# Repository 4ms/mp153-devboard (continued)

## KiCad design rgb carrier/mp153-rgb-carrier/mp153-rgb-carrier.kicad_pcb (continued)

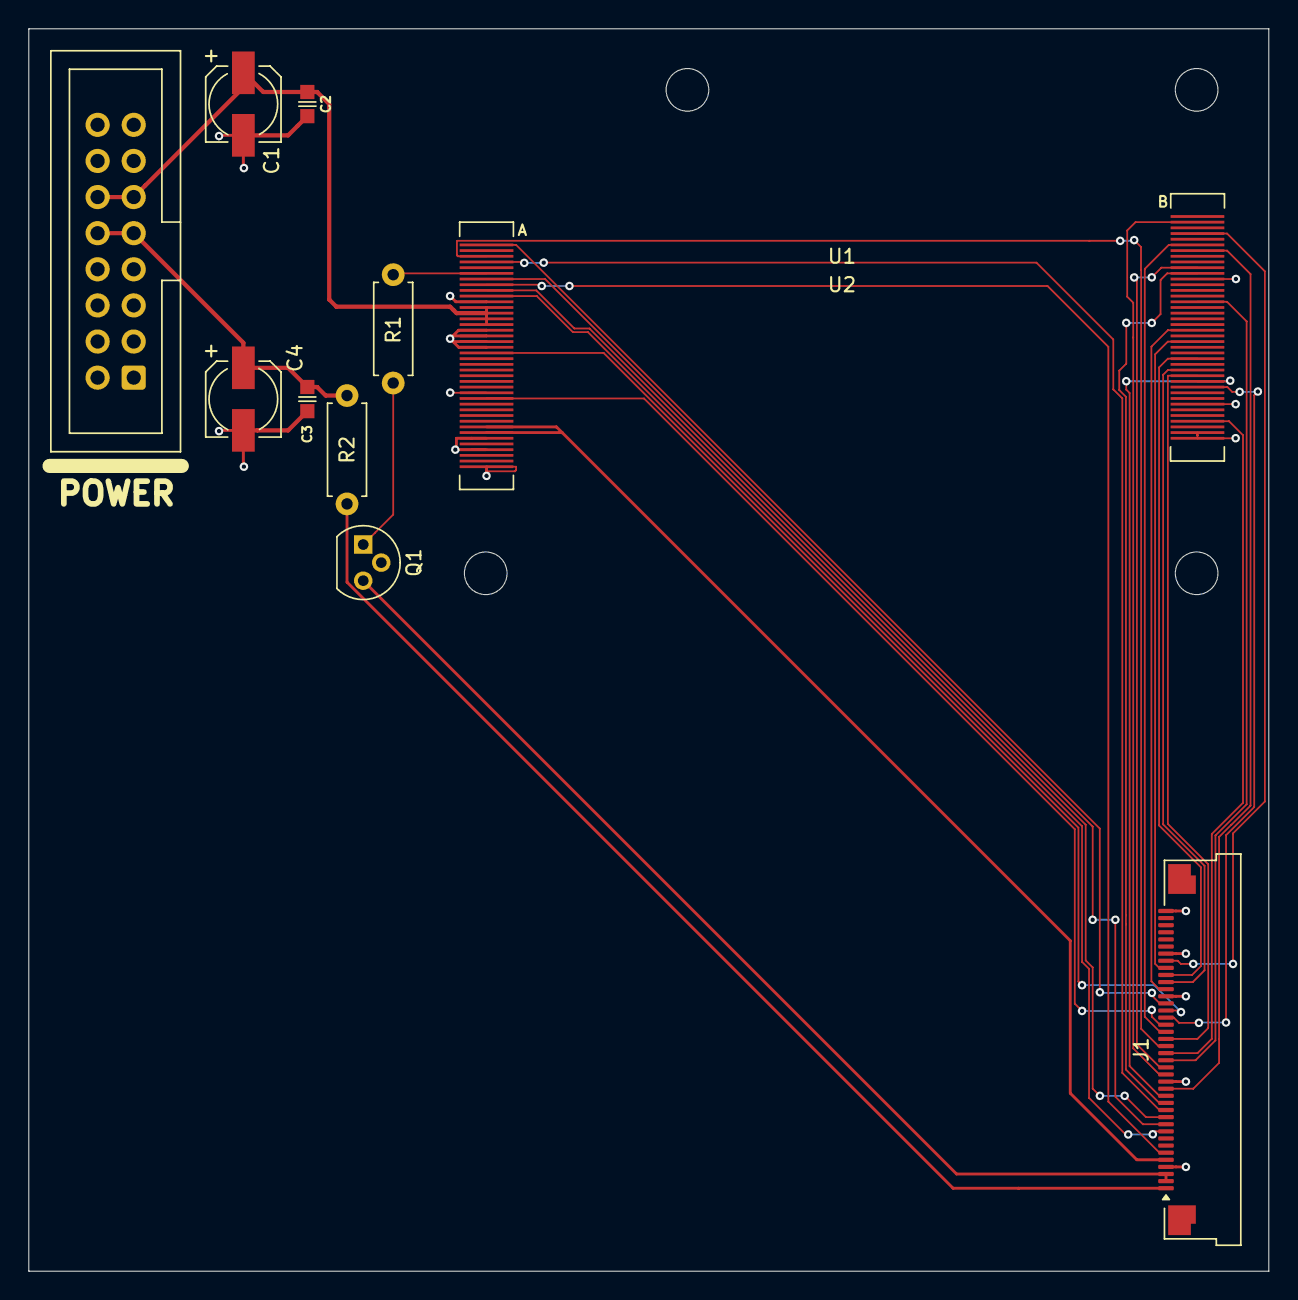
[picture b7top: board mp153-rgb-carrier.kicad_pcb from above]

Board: 2 copper layers, 87.2 x 87.4 mm, 11 parts (0 on the bottom side), 32 nets.

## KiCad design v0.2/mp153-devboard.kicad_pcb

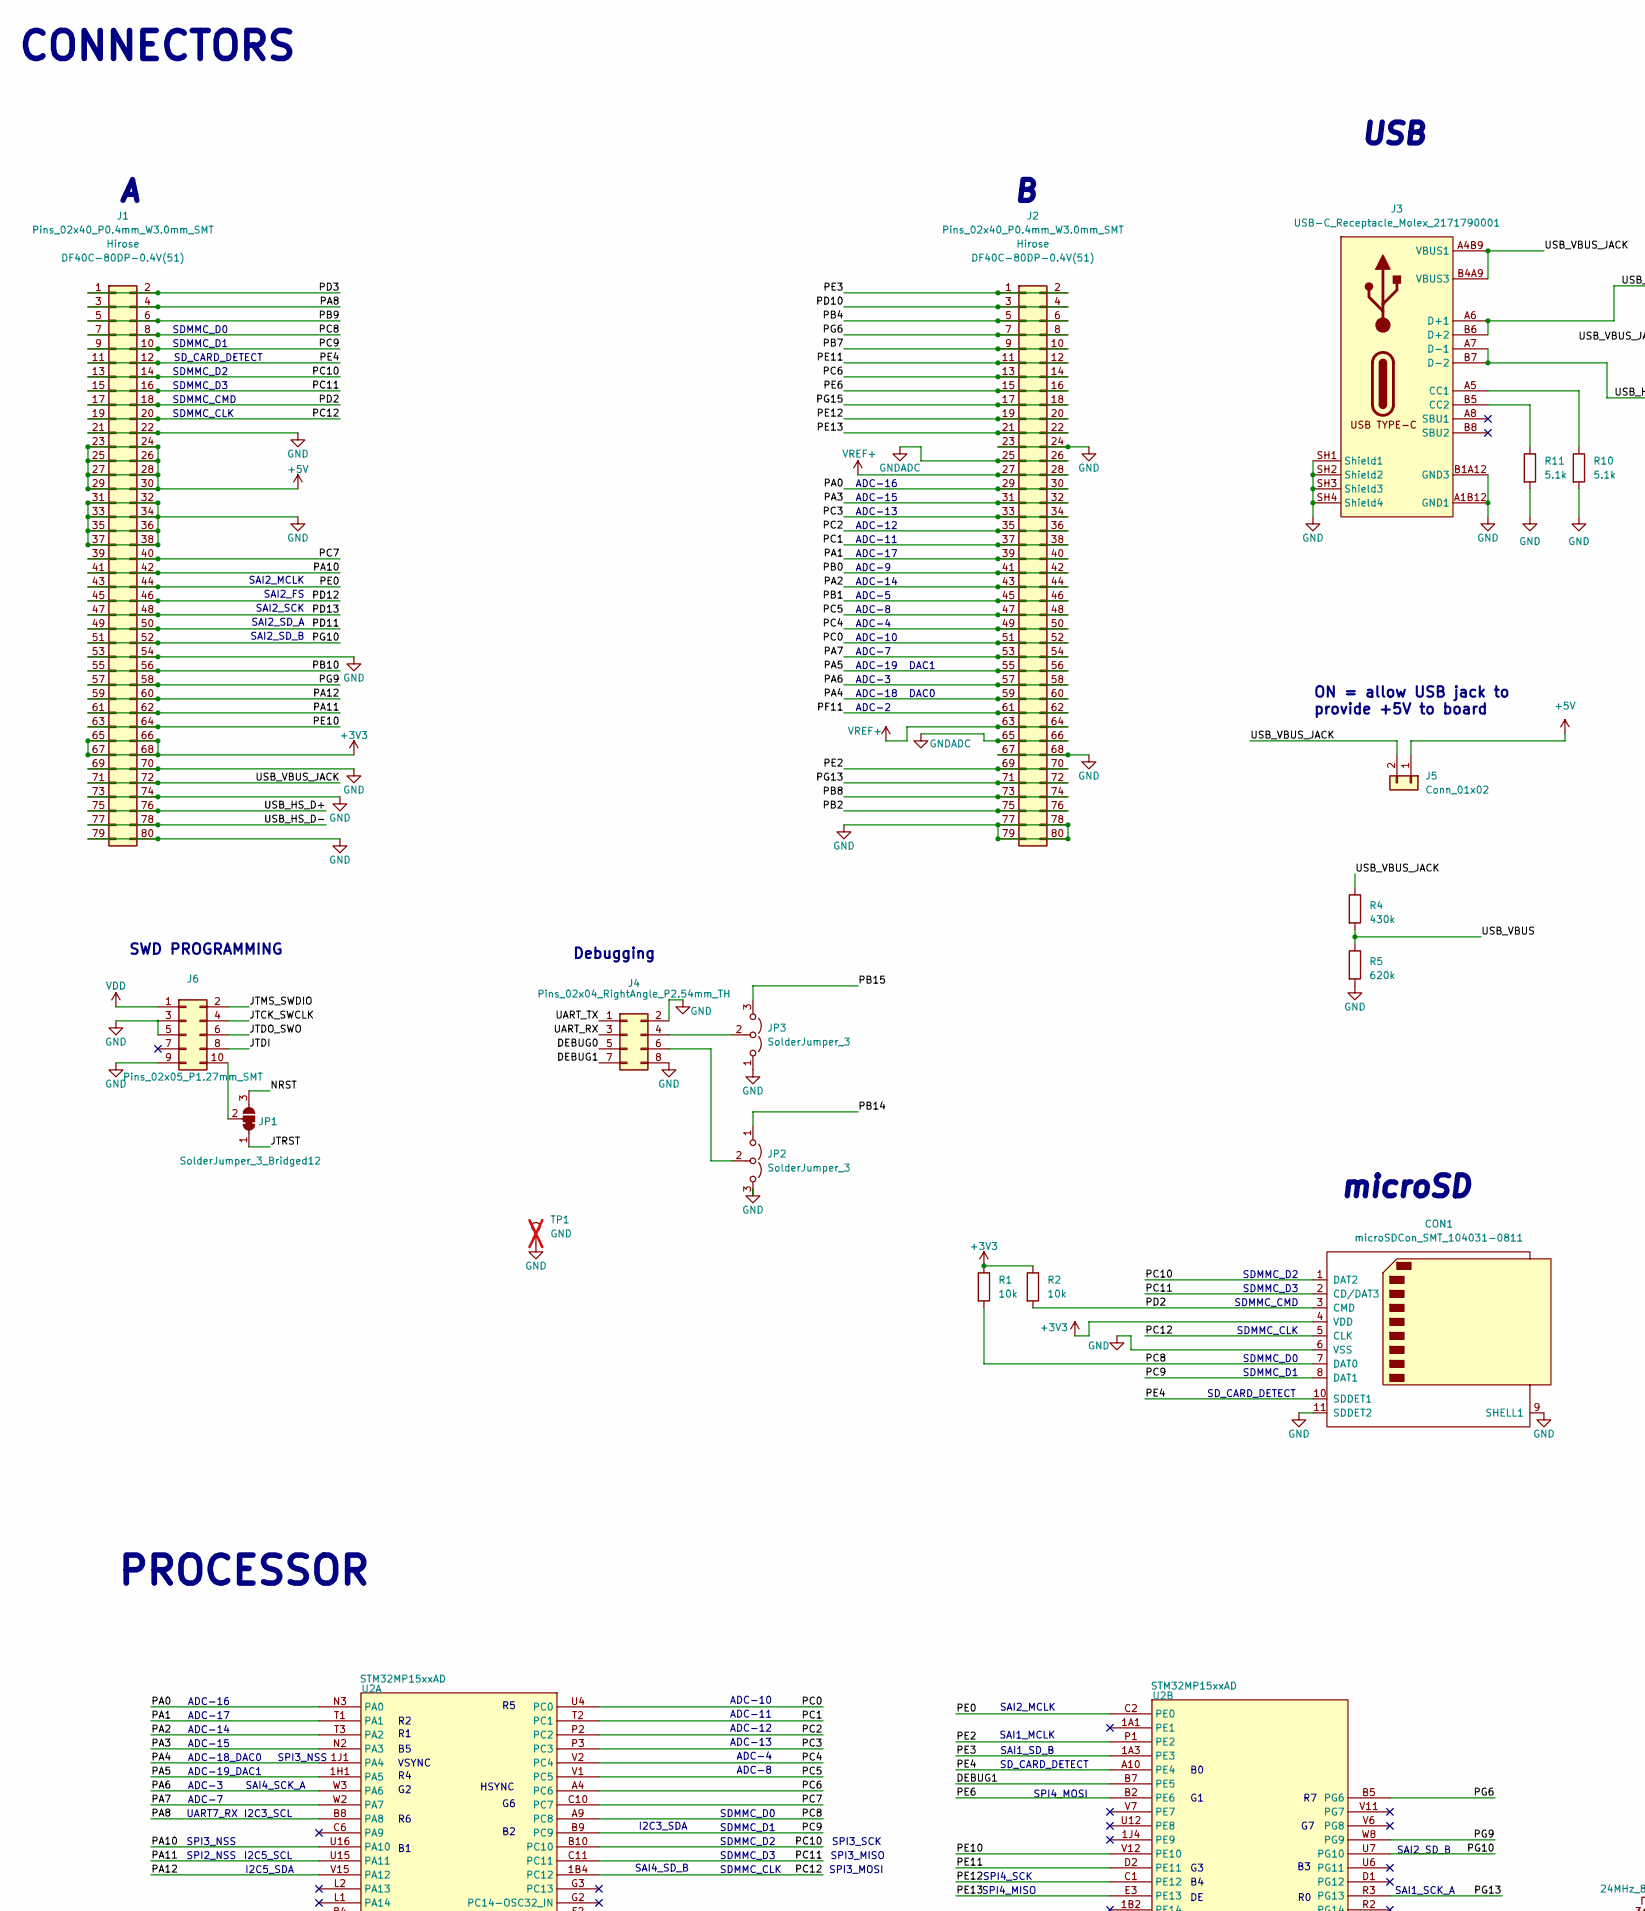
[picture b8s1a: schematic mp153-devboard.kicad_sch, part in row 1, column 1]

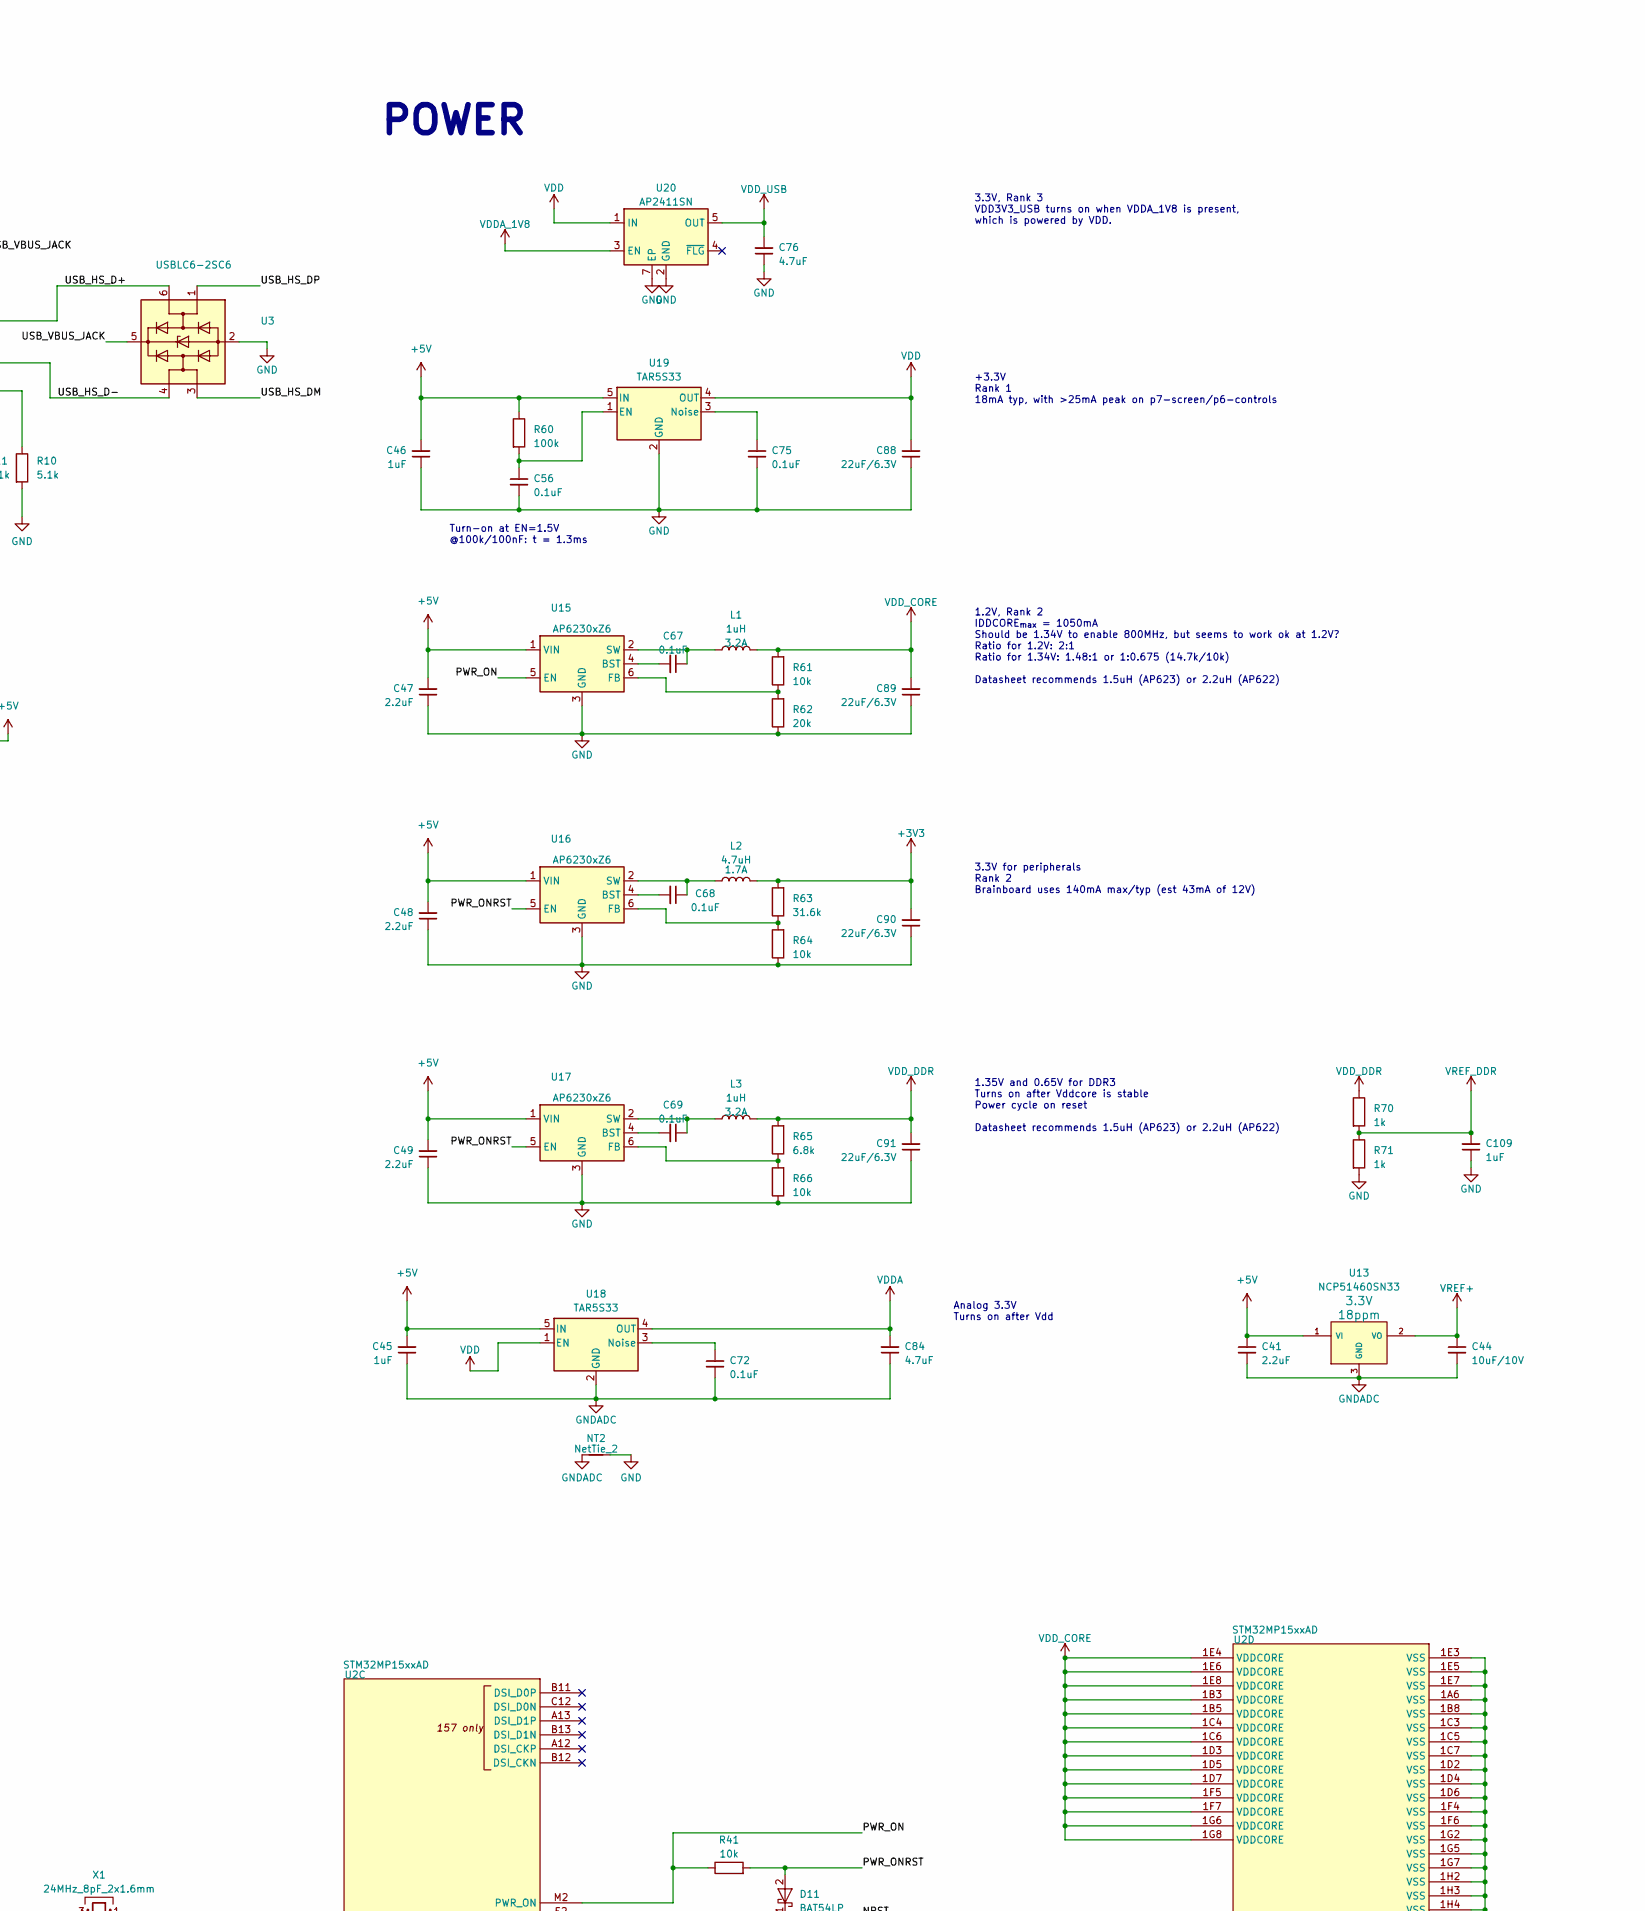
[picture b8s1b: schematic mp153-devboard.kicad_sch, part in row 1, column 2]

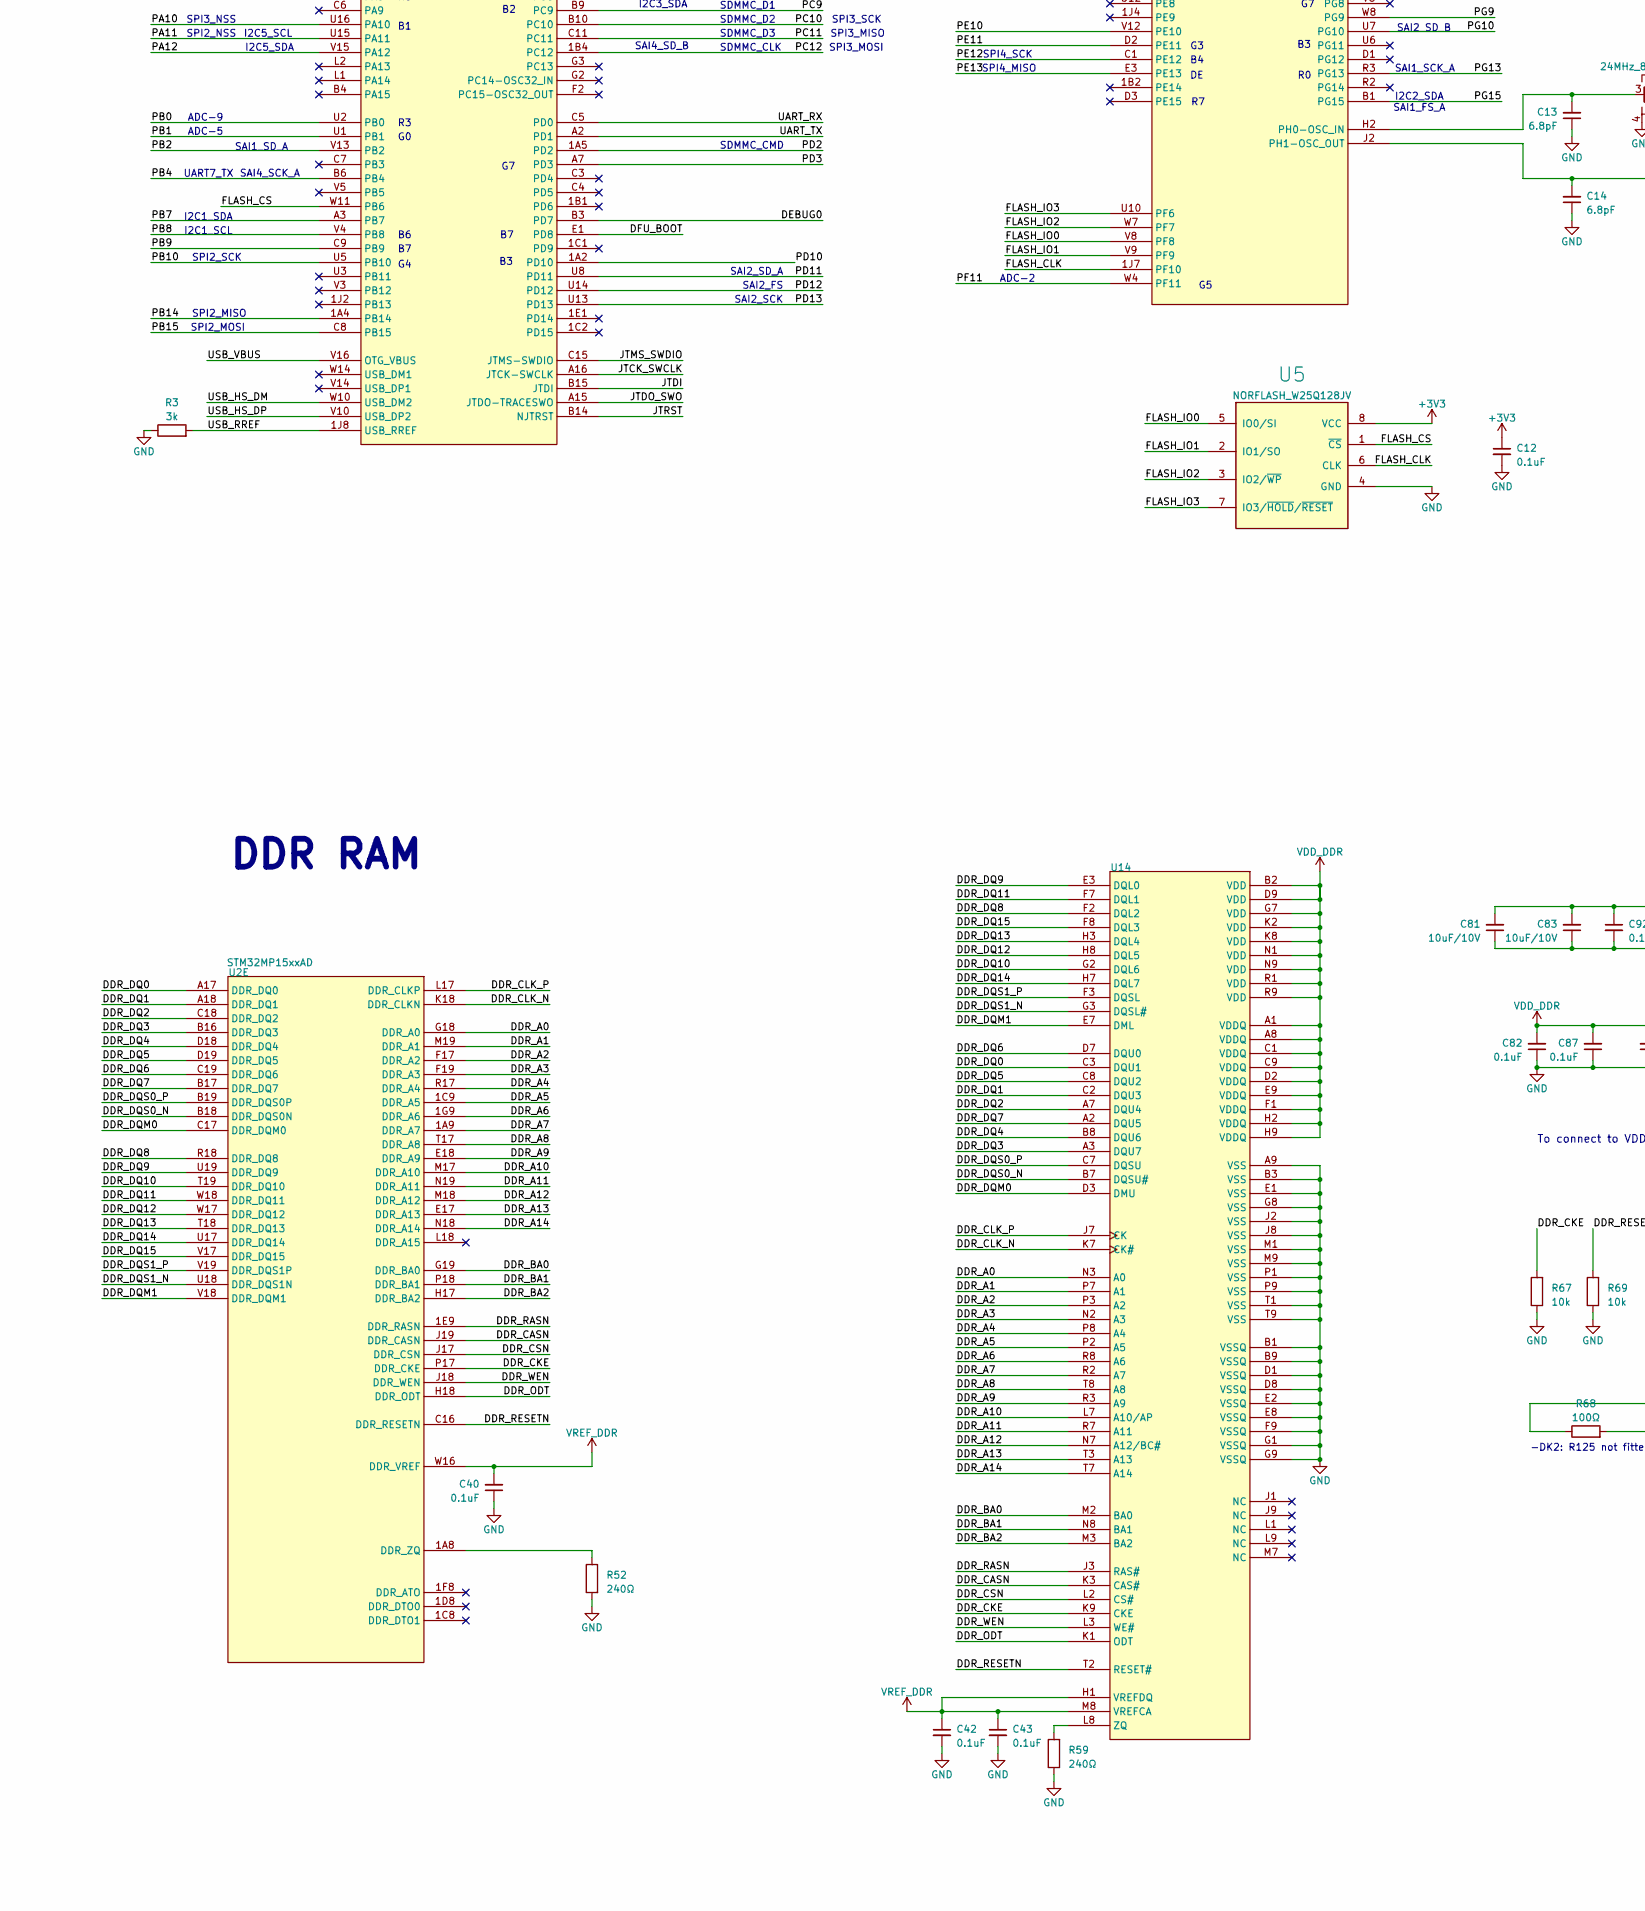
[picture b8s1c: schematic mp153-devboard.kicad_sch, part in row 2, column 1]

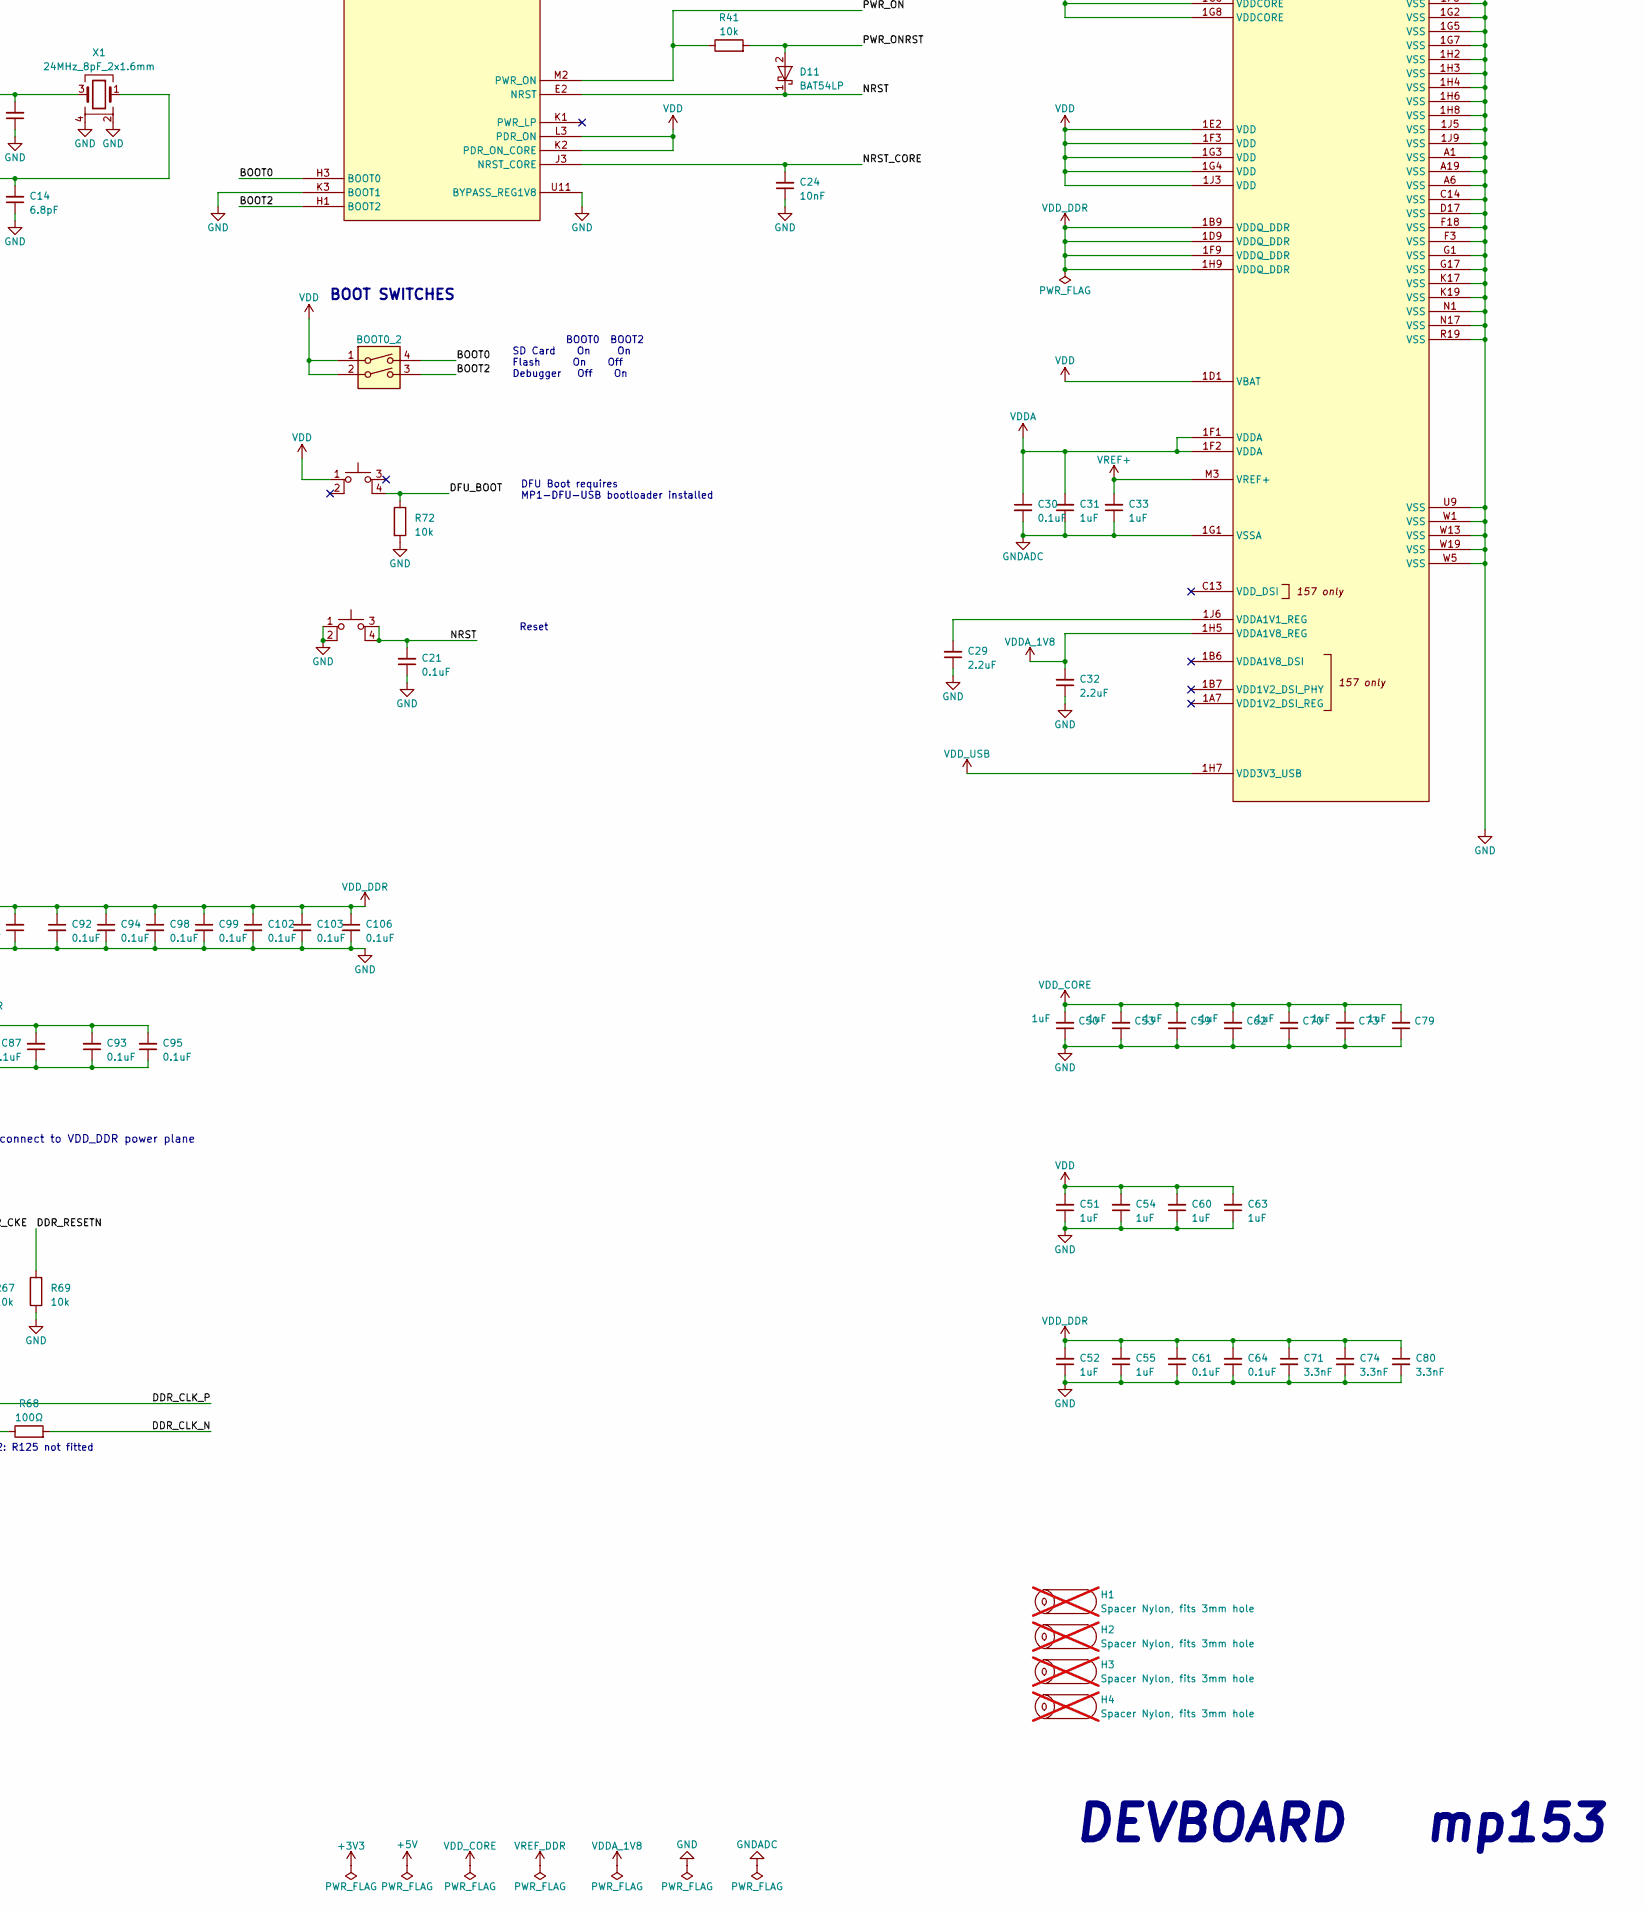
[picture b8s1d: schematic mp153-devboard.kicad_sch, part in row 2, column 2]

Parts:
BOOT0_2: SW_DIP_x02_CTS_219-2MST; SW_DIP_SPSTx02_CTS_219-2MSTR; Part Number 219-2MST; JLCPCB ID C2961978
C12, C21, C30, C40, C42, C43, C61, C64, C67, C68, C69, C82, C87, C92, C93, C94, C95, C98, C99, C102, C103, C106: 100nF_0402_16V; C_0402; Part Number GCM155R71C104KA55D; JLCPCB ID C1525
C13, C14: 6.8pF_0402_25V; C_0402; Part Number CC0402CRNPO9BN6R8; JLCPCB ID C1576
C24: 10nF_0402_16V; C_0402; Part Number CC0402KRX7R7BB103; JLCPCB ID C15195
C29, C32: 2.2uF_0402_6.3V; C_0402; Part Number GRM155R60J225KE95D; JLCPCB ID C12530
C31, C33, C45, C46, C50, C51, C52, C53, C54, C55, C59, C60, C62, C63, C70, C73, C79, C109: 1uF_0402_25V; C_0402; Part Number GMK105CC6105KV-F; JLCPCB ID C52923
C41, C47, C48, C49: 2.2uF_0603_25V; C_0603; Part Number GRM188R6YA225KA12D; JLCPCB ID C57895
C44, C81, C83: 10uF_0603_10V; C_0603; Part Number GRM188R61A106KE69D; JLCPCB ID C19702
C56, C72, C75: 100nF_0402_50V; C_0402; Part Number GRM155R71H104KE14D; JLCPCB ID C307331
C71, C74, C80: 3.3nF_0402_16V; C_0402; Part Number VJ0402Y332KXACW1BC; JLCPCB ID C26404
C76, C84: 4.7uF_0402_6.3V; C_0402; Part Number GRM155R60J475ME47; JLCPCB ID C23733
C88, C89, C90, C91: 22uF_0603_6.3V; C_0603; Part Number GRM188R60J226MEA0J; JLCPCB ID C59461
CON1: microSDCon_SMT_104031-0811; CardSlot_MicroSD_Molex_104031-0811; Part Number 104031-0811; JLCPCB ID C585350
D11: BAT54LP; DFN-1006-2; Part Number BAT54LP-7; JLCPCB ID C134410
H1, H2, H3, H4: Spacer Nylon, fits 3mm hole; MountingHole_Generic_3mm; not fitted
J1, J2: Pins_02x40_P0.4mm_W3.0mm_SMT; Connector-80pin-P0.4mm-W3.0mm; Part Number DF40C-80DP-0.4V(51); JLCPCB ID C294544
J3: USB-C_Receptacle_Molex_2171790001; USB_C_Receptacle_Molex_2171790001; Part Number 217179-0001; JLCPCB ID C2894899
J4: Pins_02x04_RightAngle_P2.54mm_TH; Pins_2x04_P2.54mm_Horizontal_CroppedSilk; Part Number TSW-104-08-T-D-RA
J5: Conn_01x02; Pins_1x02_2.54mm_TH; Part Number TSW-102-08-T-S-RA
J6: Pins_02x05_P1.27mm_SMT; Pins_2x05_1.27mm_SMD; Part Number FTSH-105-01-F-DV; JLCPCB ID C598540
JP1: SolderJumper_3_Bridged12; JUMPER_SMD_1x3_tiny
JP2, JP3: SolderJumper_3; JUMPER_SMD_1x3_tiny_open
L1, L3: 1uH_3.2A_2520; L_1008_2520Metric; Part Number DFE252012P-1R0M=P2; JLCPCB ID C435392
L2: 4.7uH_1.7A_2510; L_Wuerth_MAPI-2510; Part Number SRN2510F-4R7M; JLCPCB ID C2047781
NT2: NetTie_2; NetTie-2_SMD_Pad0.16mm_6mil
R1, R2, R41, R61, R64, R66, R67, R69, R72: 10k_0402; R_0402; Part Number RC0402FR-0710KL; JLCPCB ID C60490
R3: 3k_0402; R_0402; Part Number RC0402FR-073KL; JLCPCB ID C137987
R4: 430k_0402; R_0402; Part Number RC0402FR-07430KL; JLCPCB ID C163463
R5: 620k_0402; R_0402; Part Number RC0402FR-07620KL; JLCPCB ID C137952
R10, R11: 5.1k_0402; R_0402; Part Number RC0402FR-075K1L; JLCPCB ID C105872
R52, R59: 240Ω_0402; R_0402; Part Number RC0402FR-07240RL; JLCPCB ID C114755
R60: 100k_0402; R_0402; Part Number RC0402FR-07100KL; JLCPCB ID C60491
R62: 20k_0402; R_0402; Part Number RC0402FR-0720KL; JLCPCB ID C93942
R63: 31.6k_0402; R_0402; Part Number RC0402FR-0731K6L; JLCPCB ID C276265
R65: 6.8k_0402; R_0402; Part Number RC0402FR-076K8L; JLCPCB ID C93940
R68: 100Ω_0402; R_0402; Part Number RC0402FR-07100RL; JLCPCB ID C106232
R70, R71: 1k_0402; R_0402; Part Number RC0402FR-071KL; JLCPCB ID C106235
S2, S3: SW_Push_PTS526 SM15 SMTR2 LFS; Button_Tact_PTS526; Part Number PTS526 SM15 SMTR2 LFS; JLCPCB ID C2689521
TP1: GND; PinHeader_1x01_P2.54mm_Vertical; not fitted
U2: STM32MP15xxAD; TFBGA-257_10x10mm_perP0.5_cntrP0.65; Part Number STM32MP153DAD; JLCPCB ID C1236719
U3: USBLC6-2SC6; SOT-23-6; Part Number USBLC6-2SC6; JLCPCB ID C2827654
U5: NORFLASH_W25Q128JV; SOIC-8_5.28x4.9mm_Pitch1.27mm; Part Number W25Q128JVSIQ; JLCPCB ID C113767
U13: NCP51460SN33; SOT23-3_PO132; Part Number NCP51460SN33T1G; JLCPCB ID C233715
U14: DDR3L-RAM-4Gb_MT41K256M16TW; FBGA-96_Layout2x3x16_Body8x14_P0.8mm; Part Number MT41K256M16TW-107-P-V00H; JLCPCB ID C253882
U15, U16, U17: AP6230xZ6; SOT-563; Part Number AP62301Z6; JLCPCB ID C1880992
U18, U19: TAR5S33; SOT-23-5; Part Number TAR5S33TE85LF; JLCPCB ID C2762700
U20: AP2411SN; DFN-6-1EP_2x2mm_P0.65mm_EP1x1.6mm; Part Number AP2411SN-7; JLCPCB ID C2149815
X1: 24MHz_8pF_2x1.6mm; Crystal_2.0x1.6mm_4pin; Part Number ECS-240-8-37-CKM-TR3; JLCPCB ID C1986107

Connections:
+3V3: C12.1, C90.2, CON1.4 (VDD), J1.65, J1.66, J1.67, J1.68, L2.2, R1.1, R2.1, R63.2, U5.8 (VCC)
+5V: C41.1, C45.2, C46.2, C47.2, C48.2, C49.2, J1.23, J1.24, J1.25, J1.26, J1.27, J1.28, J1.29, J1.30, J5.1, R60.1, U13.1 (VI), U15.1 (VIN), U16.1 (VIN), U17.1 (VIN), U18.5 (IN), U19.5 (IN)
/BOOT0: BOOT0_2.4, U2.H3 (BOOT0)
/BOOT2: BOOT0_2.3, U2.H1 (BOOT2)
/DDR_A0: U2.G18 (DDR_A0), U14.N3 (A0)
/DDR_A1: U2.M19 (DDR_A1), U14.P7 (A1)
/DDR_A2: U2.F17 (DDR_A2), U14.P3 (A2)
/DDR_A3: U2.F19 (DDR_A3), U14.N2 (A3)
/DDR_A4: U2.R17 (DDR_A4), U14.P8 (A4)
/DDR_A5: U2.1C9 (DDR_A5), U14.P2 (A5)
/DDR_A6: U2.1G9 (DDR_A6), U14.R8 (A6)
/DDR_A7: U2.1A9 (DDR_A7), U14.R2 (A7)
/DDR_A8: U2.T17 (DDR_A8), U14.T8 (A8)
/DDR_A9: U2.E18 (DDR_A9), U14.R3 (A9)
/DDR_A10: U2.M17 (DDR_A10), U14.L7 (A10/AP)
/DDR_A11: U2.N19 (DDR_A11), U14.R7 (A11)
/DDR_A12: U2.M18 (DDR_A12), U14.N7 (A12/BC#)
/DDR_A13: U2.E17 (DDR_A13), U14.T3 (A13)
/DDR_A14: U2.N18 (DDR_A14), U14.T7 (A14)
/DDR_BA0: U2.G19 (DDR_BA0), U14.M2 (BA0)
/DDR_BA1: U2.P18 (DDR_BA1), U14.N8 (BA1)
/DDR_BA2: U2.H17 (DDR_BA2), U14.M3 (BA2)
/DDR_CASN: U2.J19 (DDR_CASN), U14.K3 (CAS#)
/DDR_CKE: R67.2, U2.P17 (DDR_CKE), U14.K9 (CKE)
/DDR_CLK_N: R68.2, U2.K18 (DDR_CLKN), U14.K7 (CK#)
/DDR_CLK_P: R68.1, U2.L17 (DDR_CLKP), U14.J7 (CK)
/DDR_CSN: U2.J17 (DDR_CSN), U14.L2 (CS#)
/DDR_DQ0: U2.A17 (DDR_DQ0), U14.C3 (DQU1)
/DDR_DQ1: U2.A18 (DDR_DQ1), U14.C2 (DQU3)
/DDR_DQ2: U2.C18 (DDR_DQ2), U14.A7 (DQU4)
/DDR_DQ3: U2.B16 (DDR_DQ3), U14.A3 (DQU7)
/DDR_DQ4: U2.D18 (DDR_DQ4), U14.B8 (DQU6)
/DDR_DQ5: U2.D19 (DDR_DQ5), U14.C8 (DQU2)
/DDR_DQ6: U2.C19 (DDR_DQ6), U14.D7 (DQU0)
/DDR_DQ7: U2.B17 (DDR_DQ7), U14.A2 (DQU5)
/DDR_DQ8: U2.R18 (DDR_DQ8), U14.F2 (DQL2)
/DDR_DQ9: U2.U19 (DDR_DQ9), U14.E3 (DQL0)
/DDR_DQ10: U2.T19 (DDR_DQ10), U14.G2 (DQL6)
/DDR_DQ11: U2.W18 (DDR_DQ11), U14.F7 (DQL1)
/DDR_DQ12: U2.W17 (DDR_DQ12), U14.H8 (DQL5)
/DDR_DQ13: U2.T18 (DDR_DQ13), U14.H3 (DQL4)
/DDR_DQ14: U2.U17 (DDR_DQ14), U14.H7 (DQL7)
/DDR_DQ15: U2.V17 (DDR_DQ15), U14.F8 (DQL3)
/DDR_DQM0: U2.C17 (DDR_DQM0), U14.D3 (DMU)
/DDR_DQM1: U2.V18 (DDR_DQM1), U14.E7 (DML)
/DDR_DQS0_N: U2.B18 (DDR_DQS0N), U14.B7 (DQSU#)
/DDR_DQS0_P: U2.B19 (DDR_DQS0P), U14.C7 (DQSU)
/DDR_DQS1_N: U2.U18 (DDR_DQS1N), U14.G3 (DQSL#)
/DDR_DQS1_P: U2.V19 (DDR_DQS1P), U14.F3 (DQSL)
/DDR_ODT: U2.H18 (DDR_ODT), U14.K1 (ODT)
/DDR_RASN: U2.1E9 (DDR_RASN), U14.J3 (RAS#)
/DDR_RESETN: R69.2, U2.C16 (DDR_RESETN), U14.T2 (RESET#)
/DDR_WEN: U2.J18 (DDR_WEN), U14.L3 (WE#)
/DEBUG0: J4.5, U2.B3 (PD7)
/DEBUG1: J4.7, U2.B7 (PE5)
/DFU_BOOT: R72.1, S3.4, U2.E1 (PD8)
/FLASH_CLK: U2.1J7 (PF10), U5.6 (CLK)
/FLASH_CS: U2.W11 (PB6), U5.1 (~CS)
/FLASH_IO0: U2.V8 (PF8), U5.5 (IO0/SI)
/FLASH_IO1: U2.V9 (PF9), U5.2 (IO1/SO)
/FLASH_IO2: U2.W7 (PF7), U5.3 (IO2/~WP)
/FLASH_IO3: U2.U10 (PF6), U5.7 (IO3/~HOLD/~RESET)
/JTCK_SWCLK: J6.4, U2.A16 (JTCK-SWCLK)
/JTDI: J6.8, U2.B15 (JTDI)
/JTDO_SWO: J6.6, U2.A15 (JTDO-TRACESWO)
/JTMS_SWDIO: J6.2, U2.C15 (JTMS-SWDIO)
/JTRST: JP1.1 (A), U2.B14 (NJTRST)
/NRST: C21.2, D11.1 (K), JP1.3 (B), S2.3, S2.4, U2.E2 (NRST)
/NRST_CORE: C24.2, U2.J3 (NRST_CORE)
/PA0: J2.29, J2.30, U2.N3 (PA0)
/PA1: J2.39, J2.40, U2.T1 (PA1)
/PA2: J2.43, J2.44, U2.T3 (PA2)
/PA3: J2.31, J2.32, U2.N2 (PA3)
/PA4: J2.59, J2.60, U2.1J1 (PA4)
/PA5: J2.55, J2.56, U2.1H1 (PA5)
/PA6: J2.57, J2.58, U2.W3 (PA6)
/PA7: J2.53, J2.54, U2.W2 (PA7)
/PA8: J1.3, J1.4, U2.B8 (PA8)
/PA10: J1.41, J1.42, U2.U16 (PA10)
/PA11: J1.61, J1.62, U2.U15 (PA11)
/PA12: J1.59, J1.60, U2.V15 (PA12)
/PB0: J2.41, J2.42, U2.U2 (PB0)
/PB1: J2.45, J2.46, U2.U1 (PB1)
/PB2: J2.75, J2.76, U2.V13 (PB2)
/PB4: J2.5, J2.6, U2.B6 (PB4)
/PB7: J2.9, J2.10, U2.A3 (PB7)
/PB8: J2.73, J2.74, U2.V4 (PB8)
/PB9: J1.5, J1.6, U2.C9 (PB9)
/PB10: J1.55, J1.56, U2.U5 (PB10)
/PB14: JP2.1 (A), U2.1A4 (PB14)
/PB15: JP3.3 (B), U2.C8 (PB15)
/PC0: J2.51, J2.52, U2.U4 (PC0)
/PC1: J2.37, J2.38, U2.T2 (PC1)
/PC2: J2.35, J2.36, U2.P2 (PC2)
/PC3: J2.33, J2.34, U2.P3 (PC3)
/PC4: J2.49, J2.50, U2.V2 (PC4)
/PC5: J2.47, J2.48, U2.V1 (PC5)
/PC6: J2.13, J2.14, U2.A4 (PC6)
/PC7: J1.39, J1.40, U2.C10 (PC7)
/PC8: CON1.7 (DAT0), J1.7, J1.8, R1.2, U2.A9 (PC8)
/PC9: CON1.8 (DAT1), J1.9, J1.10, U2.B9 (PC9)
/PC10: CON1.1 (DAT2), J1.13, J1.14, U2.B10 (PC10)
/PC11: CON1.2 (CD/DAT3), J1.15, J1.16, U2.C11
/PC12: CON1.5 (CLK), J1.19, J1.20, U2.1B4 (PC12)
/PD2: CON1.3 (CMD), J1.17, J1.18, R2.2, U2.1A5 (PD2)
/PD3: J1.1, J1.2, U2.A7 (PD3)
/PD10: J2.3, J2.4, U2.1A2 (PD10)
/PD11: J1.49, J1.50, U2.U8 (PD11)
/PD12: J1.45, J1.46, U2.U14 (PD12)
/PD13: J1.47, J1.48, U2.U13 (PD13)
/PE0: J1.43, J1.44, U2.C2 (PE0)
/PE2: J2.69, J2.70, U2.P1 (PE2)
/PE3: J2.1, J2.2, U2.1A3 (PE3)
/PE4: CON1.10 (SDDET1), J1.11, J1.12, U2.A10 (PE4)
/PE6: J2.15, J2.16, U2.B2 (PE6)
/PE10: J1.63, J1.64, U2.V12 (PE10)
/PE11: J2.11, J2.12, U2.D2 (PE11)
/PE12: J2.19, J2.20, U2.C1 (PE12)
/PE13: J2.21, J2.22, U2.E3 (PE13)
/PF11: J2.61, J2.62, U2.W4 (PF11)
/PG6: J2.7, J2.8, U2.B5 (PG6)
/PG9: J1.57, J1.58, U2.W8 (PG9)
/PG10: J1.51, J1.52, U2.U7 (PG10)
/PG13: J2.71, J2.72, U2.R3 (PG13)
/PG15: J2.17, J2.18, U2.B1 (PG15)
/PWR_ON: R41.1, U2.M2 (PWR_ON), U15.5 (EN)
/PWR_ONRST: D11.2 (A), R41.2, U16.5 (EN), U17.5 (EN)
/UART_RX: J4.3, U2.C5 (PD0)
/UART_TX: J4.1, U2.A2 (PD1)
/USB_HS_D+: J1.75, J1.76, J3.A6 (D+1), J3.B6 (D+2), U3.6 (I/O1)
/USB_HS_D-: J1.77, J1.78, J3.A7 (D-1), J3.B7 (D-2), U3.4 (I/O2)
/USB_HS_DM: U2.W10 (USB_DM2), U3.3 (I/O2)
/USB_HS_DP: U2.V10 (USB_DP2), U3.1 (I/O1)
/USB_RREF: R3.2, U2.1J8 (USB_RREF)
/USB_VBUS: R4.2, R5.1, U2.V16 (OTG_VBUS)
/USB_VBUS_JACK: J1.71, J1.72, J3.A4B9 (VBUS1), J3.B4A9 (VBUS3), J5.2, R4.1, U3.5 (VBUS)
GND: C12.2, C13.1, C14.1, C21.1, C24.1, C29.1, C32.1, C40.1, C42.2, C43.2, C46.1, C47.1, C48.1, C49.1, C50.1, C51.1, C52.1, C53.1, C54.1, C55.1, C56.2, C59.1, C60.1, C61.1, C62.1, C63.1, C64.1, C70.1, C71.2, C73.1, C74.2, C75.2, C76.1, C79.1, C80.2, C81.1, C82.1, C83.1, C87.1, C88.1, C89.1, C90.1, C91.1, C92.2, C93.1, C94.2, C95.1, C98.2, C99.2, C102.2, C103.2, C106.2, C109.1, CON1.6 (VSS), CON1.9 (SHELL1), CON1.11 (SDDET2), J1.21, J1.22, J1.31, J1.32, J1.33, J1.34, J1.35, J1.36, J1.37, J1.38, J1.53, J1.54, J1.69, J1.70, J1.73, J1.74, J1.79, J1.80, J2.23, J2.24, J2.67, J2.68, J2.77, J2.78, J2.79, J2.80, J3.A1B12 (GND1), J3.B1A12 (GND3), J3.SH1 (Shield1), J3.SH2 (Shield2), J3.SH3 (Shield3), J3.SH4 (Shield4), J4.2, J4.8, J6.3, J6.5, J6.9, JP2.3 (B), JP3.1 (A), NT2.2, R3.1, R5.2, R10.2, R11.2, R52.2, R59.1, R62.1, R64.1, R66.1, R67.1, R69.1, R71.2, R72.2, S2.1, S2.2, TP1.1, U2.1A6 (VSS), U2.1B8 (VSS), U2.1C3 (VSS), U2.1C5 (VSS), U2.1C7 (VSS), U2.1D2 (VSS), U2.1D4 (VSS), U2.1D6 (VSS), U2.1E3 (VSS), U2.1E5 (VSS), U2.1E7 (VSS), U2.1F4 (VSS), U2.1F6 (VSS), U2.1G2 (VSS), U2.1G5 (VSS), U2.1G7 (VSS), U2.1H2 (VSS), U2.1H3 (VSS), U2.1H4 (VSS), U2.1H6 (VSS), U2.1H8 (VSS), U2.1J5 (VSS), U2.1J9 (VSS), U2.A1 (VSS), U2.A6 (VSS), U2.A19 (VSS), U2.C14 (VSS), U2.D17 (VSS), U2.F3 (VSS), U2.F18 (VSS), U2.G1 (VSS), U2.G17 (VSS), U2.K3 (BOOT1), U2.K17 (VSS), U2.K19 (VSS), U2.N1 (VSS), U2.N17 (VSS), U2.R19 (VSS), U2.U9 (VSS), U2.U11 (BYPASS_REG1V8), U2.W1 (VSS), U2.W5 (VSS), U2.W13 (VSS), U2.W19 (VSS), U3.2 (GND), U5.4 (GND), U14.A9 (VSS), U14.B1 (VSSQ), U14.B3 (VSS), U14.B9 (VSSQ), U14.D1 (VSSQ), U14.D8 (VSSQ), U14.E1 (VSS), U14.E2 (VSSQ), U14.E8 (VSSQ), U14.F9 (VSSQ), U14.G1 (VSSQ), U14.G8 (VSS), U14.G9 (VSSQ), U14.J2 (VSS), U14.J8 (VSS), U14.M1 (VSS), U14.M9 (VSS), U14.P1 (VSS), U14.P9 (VSS), U14.T1 (VSS), U14.T9 (VSS), U15.3 (GND), U16.3 (GND), U17.3 (GND), U19.2 (GND), U20.2 (GND), U20.7 (EP), X1.2, X1.4
GNDADC: C30.2, C31.1, C33.1, C41.2, C44.2, C45.1, C72.2, C84.1, J2.25, J2.26, J2.65, J2.66, NT2.1, U2.1G1 (VSSA), U13.3 (GND), U18.2 (GND)
unnamed: J3.A5 (CC1), R10.1
unnamed: J3.B5 (CC2), R11.1
unnamed: J4.4, JP3.2 (C)
unnamed: J4.6, JP2.2 (C)
unnamed: J6.10, JP1.2 (C)
unnamed: C13.2, U2.H2 (PH0-OSC_IN), X1.3
unnamed: C14.2, U2.J2 (PH1-OSC_OUT), X1.1
unnamed: C29.2, U2.1J6 (VDDA1V1_REG)
unnamed: R52.1, U2.1A8 (DDR_ZQ)
unnamed: R59.2, U14.L8 (ZQ)
unnamed: C67.2, U15.4 (BST)
unnamed: R61.1, R62.2, U15.6 (FB)
unnamed: C67.1, L1.1, U15.2 (SW)
unnamed: C68.2, U16.4 (BST)
unnamed: R63.1, R64.2, U16.6 (FB)
unnamed: C68.1, L2.1, U16.2 (SW)
unnamed: C69.2, U17.4 (BST)
unnamed: R65.1, R66.2, U17.6 (FB)
unnamed: C69.1, L3.1, U17.2 (SW)
unnamed: C72.1, U18.3 (Noise)
unnamed: C56.1, R60.2, U19.1 (EN)
unnamed: C75.1, U19.3 (Noise)
VDD: BOOT0_2.1, BOOT0_2.2, C51.2, C54.2, C60.2, C63.2, C88.2, J6.1, S3.1, U2.1D1 (VBAT), U2.1E2 (VDD), U2.1F3 (VDD), U2.1G3 (VDD), U2.1G4 (VDD), U2.1J3 (VDD), U2.K2 (PDR_ON_CORE), U2.L3 (PDR_ON), U18.1 (EN), U19.4 (OUT), U20.1 (IN)
VDDA: C30.1, C31.2, C84.2, U2.1F1 (VDDA), U2.1F2 (VDDA), U18.4 (OUT)
VDDA_1V8: C32.2, U2.1H5 (VDDA1V8_REG), U20.3 (EN)
VDD_CORE: C50.2, C53.2, C59.2, C62.2, C70.2, C73.2, C79.2, C89.2, L1.2, R61.2, U2.1B3 (VDDCORE), U2.1B5 (VDDCORE), U2.1C4 (VDDCORE), U2.1C6 (VDDCORE), U2.1D3 (VDDCORE), U2.1D5 (VDDCORE), U2.1D7 (VDDCORE), U2.1E4 (VDDCORE), U2.1E6 (VDDCORE), U2.1E8 (VDDCORE), U2.1F5 (VDDCORE), U2.1F7 (VDDCORE), U2.1G6 (VDDCORE), U2.1G8 (VDDCORE)
VDD_DDR: C52.2, C55.2, C61.2, C64.2, C71.1, C74.1, C80.1, C81.2, C82.2, C83.2, C87.2, C91.2, C92.1, C93.2, C94.1, C95.2, C98.1, C99.1, C102.1, C103.1, C106.1, L3.2, R65.2, R70.1, U2.1B9 (VDDQ_DDR), U2.1D9 (VDDQ_DDR), U2.1F9 (VDDQ_DDR), U2.1H9 (VDDQ_DDR), U14.A1 (VDDQ), U14.A8 (VDDQ), U14.B2 (VDD), U14.C1 (VDDQ), U14.C9 (VDDQ), U14.D2 (VDDQ), U14.D9 (VDD), U14.E9 (VDDQ), U14.F1 (VDDQ), U14.G7 (VDD), U14.H2 (VDDQ), U14.H9 (VDDQ), U14.K2 (VDD), U14.K8 (VDD), U14.N1 (VDD), U14.N9 (VDD), U14.R1 (VDD), U14.R9 (VDD)
VDD_USB: C76.2, U2.1H7 (VDD3V3_USB), U20.5 (OUT)
VREF+: C33.2, C44.1, J2.27, J2.28, J2.63, J2.64, U2.M3 (VREF+), U13.2 (VO)
VREF_DDR: C40.2, C42.1, C43.1, C109.2, R70.2, R71.1, U2.W16 (DDR_VREF), U14.H1 (VREFDQ), U14.M8 (VREFCA)

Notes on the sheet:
SPI2_SCK
SPI3_SCK
DFU Boot requires MP1-DFU-USB bootloader installed
SPI4_SCK
SDMMC_CMD
DAC0
microSD
I2C1_SDA
ADC-5
SAI2_SD_B
SPI3_NSS
SPI3_MOSI
SAI2_MCLK
POWER
SAI2_FS
I2C2_SDA
SD_CARD_DETECT
ADC-18_DAC0
ADC-15
ADC-8
SAI1_SD_A
BOOT SWITCHES
SPI4_MISO
HSYNC
mp153
ADC-4
ADC-16
ADC-19_DAC1
SDMMC_D1
ADC-17
SAI2_SD_A
SDMMC_D3
ADC-14
SAI1_SCK_A
-DK2: R125 not fitted
SWD PROGRAMMING
3.3V for peripherals Rank 2 Brainboard uses 140mA max/typ (est 43mA of 12V)
ADC-9
CONNECTORS
SDMMC_CLK
